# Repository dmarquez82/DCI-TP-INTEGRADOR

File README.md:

## Trabajo práctico final de la asignatura DCI ##
Este repositorio contiene el trabajo práctico final para la asignatura de Diseño de Circuitos Impresos de la carrera de posgrado de FIUBA.

* Autor: Prof. Ing. Daniel Márquez
* Título corto del trabajo: Placa carrier para ESP32-S3 DevKit
* Descripción: placa base (carrier) para la placa de desarrollo ESP32-S3 DevKit de 44 pines, pensada para su uso en las cátedras de la universidad. Expande todos los pines de la DevKit en dos tiras hembra rotuladas y agrega los periféricos que se usan en las prácticas: entrada de alimentación de 12 V con regulador a 5 V (la placa funciona sin necesidad de conectar el USB), dos LEDs, dos pulsadores, una salida a relé inversor de 220 V con LED indicador, una entrada analógica de 0–10 V protegida, un sensor DHT11 y un transceptor CAN (MCP2562) con terminación de 120 Ω seleccionable por jumper. PCB de dos capas con componentes solo en la cara superior.
* Cursada: OCT-NOV-DIC 2026

## Licencia de este trabajo ##
Este diseño de hardware se distribuye bajo la licencia **GNU General Public License v3.0 o posterior** (GPL-3.0-or-later). El texto completo está en el archivo [LICENSE](LICENSE).

Para este diseño, el "código fuente" en el sentido de la licencia son los archivos del proyecto KiCad que están en el directorio [pcb](pcb) (`.kicad_pro`, `.kicad_sch` y `.kicad_pcb`).

Las hojas de datos del directorio [info](info) son de sus respectivos fabricantes y no están alcanzadas por esta licencia.

## Estructura del repositorio ##

* [doc](doc): documentación propia del trabajo. En [doc/propuesta](doc/propuesta) está la propuesta presentada a la cátedra.
* [info](info): hojas de datos de los componentes principales (relé, transistor, regulador y transceptor CAN) y pinout de la placa ESP32-S3.
* [pcb](pcb): proyecto KiCad con el esquemático y el PCB.

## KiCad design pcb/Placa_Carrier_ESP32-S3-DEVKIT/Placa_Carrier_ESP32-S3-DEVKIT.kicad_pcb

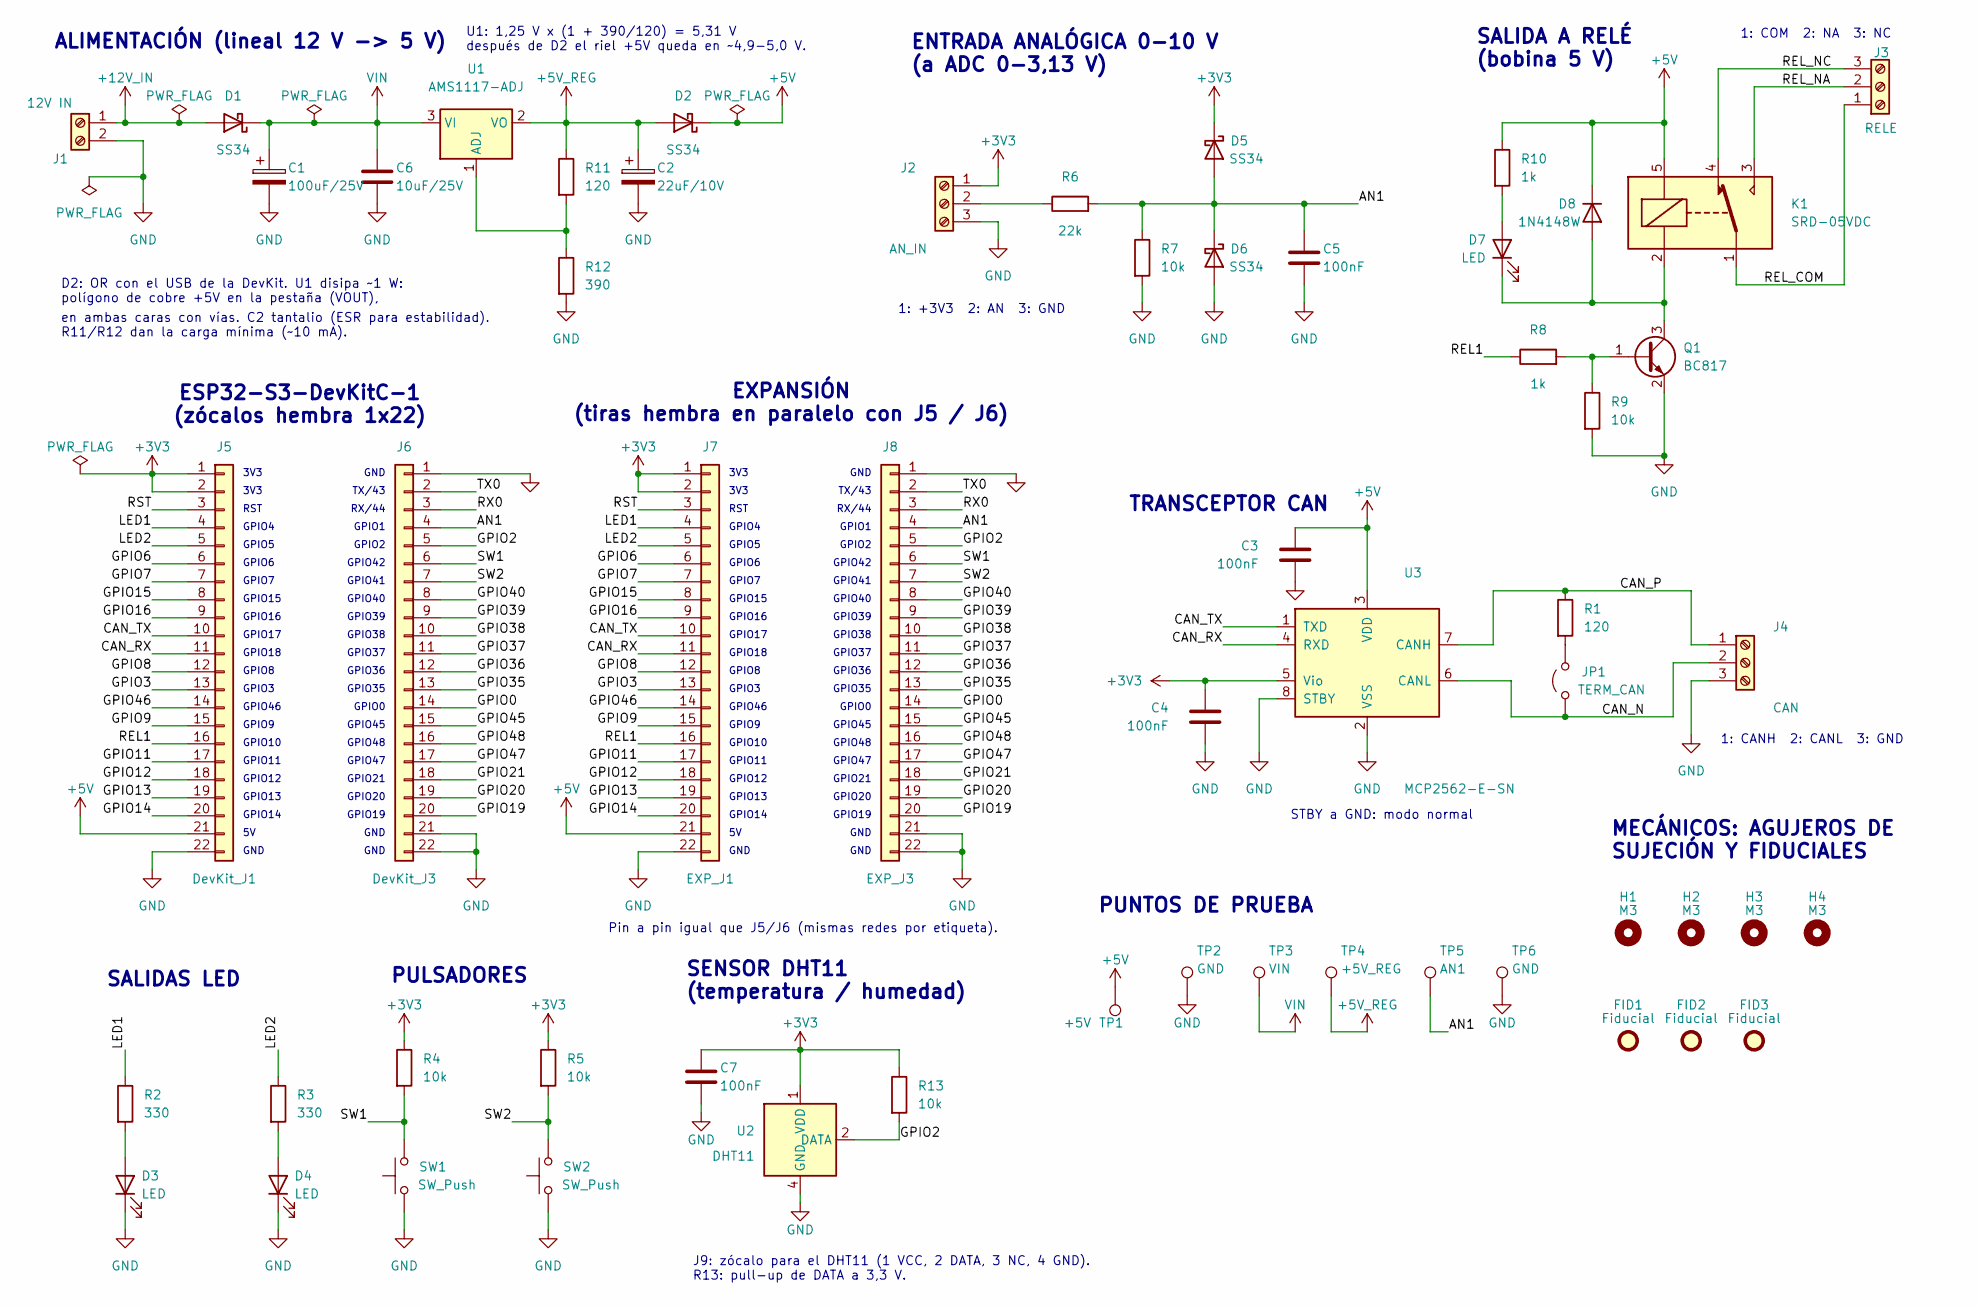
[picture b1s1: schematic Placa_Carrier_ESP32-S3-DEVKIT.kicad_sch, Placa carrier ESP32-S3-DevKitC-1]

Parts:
C1: 100uF/25V; CP_Elec_6.3x7.7
C2: 22uF/10V; CP_EIA-3528-21_Kemet-B
C3, C4, C5, C7: 100nF; C_0805_2012Metric_Pad1.18x1.45mm_HandSolder
C6: 10uF/25V; C_1206_3216Metric_Pad1.33x1.80mm_HandSolder
D1, D2, D5, D6: SS34; D_SMA
D3, D4, D7: LED; LED_1206_3216Metric_Pad1.42x1.75mm_HandSolder
D8: 1N4148W; D_SOD-123
FID1, FID2, FID3: Fiducial; Fiducial_1mm_Mask2mm
H1, H2, H3, H4: M3; MountingHole_3.2mm_M3
J1: 12V IN; TerminalBlock_Phoenix_MKDS-1,5-2-5.08_1x02_P5.08mm_Horizont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
J2: AN_IN; TerminalBlock_Phoenix_MKDS-1,5-3-5.08_1x03_P5.08mm_Horizont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
J3: RELE; TerminalBlock_Phoenix_MKDS-1,5-3-5.08_1x03_P5.08mm_Horizont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
J4: CAN; TerminalBlock_Phoenix_MKDS-1,5-3-5.08_1x03_P5.08mm_Horizont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
J5: DevKit_J1; PinSocket_1x22_P2.54mm_Vertical
J6: DevKit_J3; PinSocket_1x22_P2.54mm_Vertical
J7: EXP_J1; PinSocket_1x22_P2.54mm_Vertical
J8: EXP_J3; PinSocket_1x22_P2.54mm_Vertical
JP1: TERM_CAN; PinHeader_1x02_P2.54mm_Vertical
K1: SRD-05VDC; Relay_SPDT_SANYOU_SRD_Series_Form_C
Q1: BC817; SOT-23
R1, R11: 120; R_1206_3216Metric_Pad1.30x1.75mm_HandSolder
R2, R3: 330; R_1206_3216Metric_Pad1.30x1.75mm_HandSolder
R4, R5, R7, R9, R13: 10k; R_1206_3216Metric_Pad1.30x1.75mm_HandSolder
R6: 22k; R_1206_3216Metric_Pad1.30x1.75mm_HandSolder
R8, R10: 1k; R_1206_3216Metric_Pad1.30x1.75mm_HandSolder
R12: 390; R_1206_3216Metric_Pad1.30x1.75mm_HandSolder
SW1, SW2: SW_Push; SW_PUSH_6mm
TP1: +5V; TestPoint_Keystone_5000-5004_Miniature
TP2, TP6: GND; TestPoint_Keystone_5000-5004_Miniature
TP3: VIN; TestPoint_Keystone_5000-5004_Miniature
TP4: +5V_REG; TestPoint_Keystone_5000-5004_Miniature
TP5: AN1; TestPoint_Keystone_5000-5004_Miniature
U1: AMS1117-ADJ; SOT-223-3_TabPin2
U2: DHT11; Aosong_DHT11_5.5x12.0_P2.54mm
U3: MCP2562-E-SN; SOIC-8_3.9x4.9mm_P1.27mm

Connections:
+3V3: C4.1, C7.1, D5.1 (K), J2.1, J5.1, J5.2, J7.1, J7.2, R4.1, R5.1, R13.1, U2.1 (VDD), U3.5 (Vio)
+5V: C3.1, D2.1 (K), D8.1 (K), J5.21, J7.21, K1.5, R10.1, TP1.1 (1_1), U3.3 (VDD)
+5V_REG: C2.1, D2.2 (A), R11.1, TP4.1 (1_1), U1.2 (VO)
+12V_IN: D1.2 (A), J1.1
/AN1: C5.1, D5.2 (A), D6.1 (K), J6.4, J8.4, R6.2, R7.1, TP5.1 (1_1)
/CAN_N: J4.2, JP1.1 (A), U3.6 (CANL)
/CAN_P: J4.1, R1.1, U3.7 (CANH)
/CAN_RX: J5.11, J7.11, U3.4 (RXD)
/CAN_TX: J5.10, J7.10, U3.1 (TXD)
/GPIO0: J6.14, J8.14
/GPIO2: J6.5, J8.5, R13.2, U2.2 (DATA)
/GPIO3: J5.13, J7.13
/GPIO6: J5.6, J7.6
/GPIO7: J5.7, J7.7
/GPIO8: J5.12, J7.12
/GPIO9: J5.15, J7.15
/GPIO11: J5.17, J7.17
/GPIO12: J5.18, J7.18
/GPIO13: J5.19, J7.19
/GPIO14: J5.20, J7.20
/GPIO15: J5.8, J7.8
/GPIO16: J5.9, J7.9
/GPIO19: J6.20, J8.20
/GPIO20: J6.19, J8.19
/GPIO21: J6.18, J8.18
/GPIO35: J6.13, J8.13
/GPIO36: J6.12, J8.12
/GPIO37: J6.11, J8.11
/GPIO38: J6.10, J8.10
/GPIO39: J6.9, J8.9
/GPIO40: J6.8, J8.8
/GPIO45: J6.15, J8.15
/GPIO46: J5.14, J7.14
/GPIO47: J6.17, J8.17
/GPIO48: J6.16, J8.16
/LED1: J5.4, J7.4, R2.1
/LED2: J5.5, J7.5, R3.1
/REL1: J5.16, J7.16, R8.1
/REL_COM: J3.1, K1.1
/REL_NA: J3.2, K1.3
/REL_NC: J3.3, K1.4
/RST: J5.3, J7.3
/RX0: J6.3, J8.3
/SW1: J6.6, J8.6, R4.2, SW1.2
/SW2: J6.7, J8.7, R5.2, SW2.2
/TX0: J6.2, J8.2
GND: C1.2, C2.2, C3.2, C4.2, C5.2, C6.2, C7.2, D3.1 (K), D4.1 (K), D6.2 (A), J1.2, J2.3, J4.3, J5.22, J6.1, J6.21, J6.22, J7.22, J8.1, J8.21, J8.22, Q1.2 (E), R7.2, R9.2, R12.2, SW1.1, SW2.1, TP2.1 (1_1), TP6.1 (1_1), U2.4 (GND), U3.2 (VSS), U3.8 (STBY)
unnamed: D3.2 (A), R2.2
unnamed: D4.2 (A), R3.2
unnamed: D7.2 (A), R10.2
unnamed: D7.1 (K), D8.2 (A), K1.2, Q1.3 (C)
unnamed: J2.2, R6.1
unnamed: JP1.2 (B), R1.2
unnamed: Q1.1 (B), R8.2, R9.1
unnamed: R11.2, R12.1, U1.1 (ADJ)
VIN: C1.1, C6.1, D1.1 (K), TP3.1 (1_1), U1.3 (VI)

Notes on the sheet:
GPIO39
GPIO38
GPIO45
GPIO15
GPIO47
Pin a pin igual que J5/J6 (mismas redes por etiqueta).
GPIO13
GPIO12
GPIO10
SALIDA A RELÉ (bobina 5 V)
GPIO2
TX/43
GPIO20
GND
GPIO17
1: CANH 2: CANL 3: GND
GPIO42
GPIO1
GPIO41
SENSOR DHT11 (temperatura / humedad)
3V3
SALIDAS LED
GPIO36
GPIO46
GPIO35
ENTRADA ANALÓGICA 0-10 V (a ADC 0-3,13 V)
GPIO19
D2: OR con el USB de la DevKit. U1 disipa ~1 W: polígono de cobre +5V en la pestaña (VOUT),
GPIO18
GPIO7
1: +3V3 2: AN 3: GND
ESP32-S3-DevKitC-1 (zócalos hembra 1x22)
GPIO8
GPIO9
GPIO5
GPIO37
GPIO40
TRANSCEPTOR CAN
EXPANSIÓN (tiras hembra en paralelo con J5 / J6)
1: COM 2: NA 3: NC

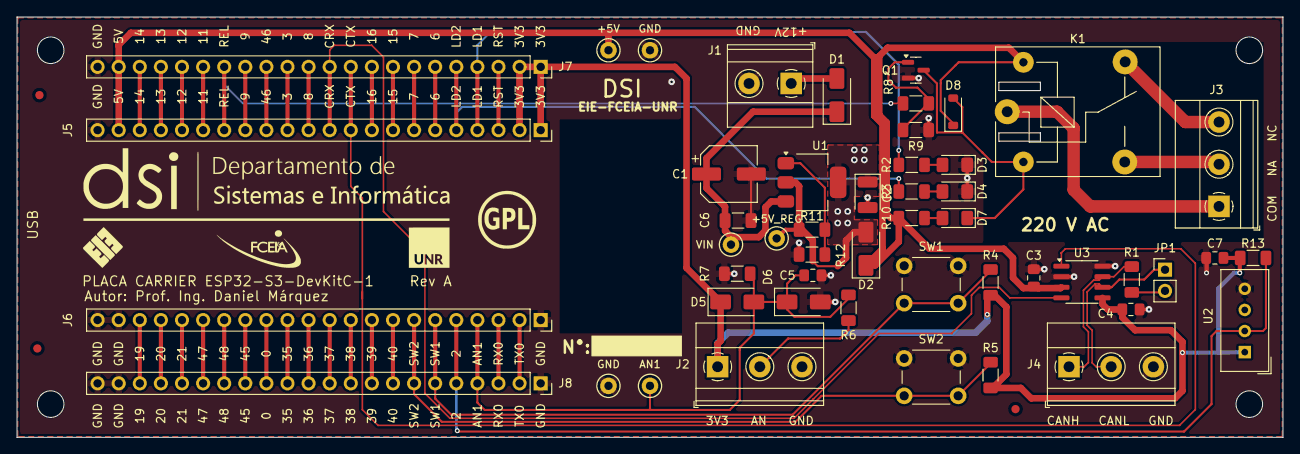
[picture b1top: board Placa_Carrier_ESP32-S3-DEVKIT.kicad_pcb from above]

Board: 2 copper layers, 152.4 x 50.6 mm, 57 parts (0 on the bottom side), 56 nets.

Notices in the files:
pcb/Placa_Carrier_ESP32-S3-DEVKIT/Placa_Carrier_ESP32-S3-DEVKIT.kicad_pcb:
Licencia: GPL
